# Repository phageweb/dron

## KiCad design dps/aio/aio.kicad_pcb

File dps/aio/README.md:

# AIO H743 pro Pavo20 Pro

Jedna deska místo MicoAir H743 AIO: STM32H743 s ArduPilotem, 4× ESC s AM32,
napájení VTX a LD06. Vychází z [OpenAIO](https://github.com/OpenDrone-hw/OpenAIO)
`986ce1e` (CERN-OHL-S-2.0), viz [návrh](../docs/02_navrh.md) a [požadavky](../docs/04_pozadavky.md).

Stav **21. 10. 2026: hlavní deska 22 nespojených, pracovní varianta MicoAir V2
po trasování 21 nespojených; obě 0 DRC chyb kategorie error.** Spoje nejsou hotové.
Nová kontrola, výsledek trasování a zbývající varování jsou v
[STAV-2026-10-21.md](./STAV-2026-10-21.md).
**Aktuální zadání: rešerše a předávka pro dokončení přes rozmístění součástek.**
Závěry, zdroje a návrh jsou v [RESERSE_LAYOUTU_V2.md](./RESERSE_LAYOUTU_V2.md),
konkrétní kroky a archiv správného výchozího projektu v
[PREDAVKA_LAYOUTU_V2.md](./PREDAVKA_LAYOUTU_V2.md). Tato předávka nahrazuje starší
doporučení pokračovat plošným přetrasováním.
Probíhá přechod k opakovatelnému postupu a referenci MicoAir743v2-AIO-45A;
připravená varianta má samostatné schéma, desku a hwdef, viz
[AUTOMATIZACE.md](./AUTOMATIZACE.md). Převzaté a jisté části jsou nakreslené,
včetně jádra H743 (napájení podle AN4938, piny podle hwdefu MicoAiru), krystalu,
barometru, druhé IMU ICM-42688-P, microSD, konektorů periferií, RGB LED a spínače bzučáku.

- **[NAVRH.md](./NAVRH.md)**: celý návrh, co je kde, proč a odkud, mapa pinů, kusovník.
- **Schéma se generuje**: `nix develop ./dps -c python3 dps/aio/gen/gen_aio.py` přepíše všechny
  listy (`*.kicad_sch`) se stálými UUID. Schéma se proto mění v `gen/gen_aio.py`, ne v KiCadu.
  Desku, pravidla, projekt a `lib.pretty` generátor nepřepisuje, ty se upravují v KiCadu.
- **[hwdef/](./hwdef/README.md)**: popis desky pro ArduPilot (firmware, bootloader, výchozí parametry).
- **Interaktivní schéma**: `nix develop ./dps -c python3 dps/aio/web/build.py` vytvoří
  `web/schema.html` (listy s klikacími bloky, texty v `web/obsah.py`).

```sh
nix develop ./dps
kicad dps/aio/aio.kicad_pro
```

## Listy

| List | Soubor | Stav | Odkud |
| --- | --- | --- | --- |
| kořen | `aio.kicad_sch` | nakreslený | vstup baterie, shunt 0,2 mΩ + INA186A3 (proud všech ESC), obrys s pady U24, testovací body z OpenAIO |
| ESC1–ESC4 | `esc_channel.kicad_sch` | **převzatý beze změny** | OpenAIO = kanál OpenESC: AT32F421 + NSG2065Q + 6× DOY180N03T, AM32 |
| Power | `fc_power.kicad_sch` | **převzatý beze změny** | +10V pro budiče ESC (stálé), +5V 3 A, USB OR na +4v5, 3,3 V TLV76733 1 A, 1,8 V pro gyro |
| IMU | `fc_imu.kicad_sch` | **převzatý beze změny** | BMI270 na SPI, napájení 1,8 V |
| VTX a LD06 | `vtx.kicad_sch` | nový | spínač TPS22810 z +10V pro HD VTX, HD VTX SH1.0-6P s pinoutem DJI, pady LD06 |
| MCU H743 | `mcu_h743.kicad_sch` | nakreslený | H743 s blokováním, krystal, BOOT0, SWD, USB-C, dělič baterie, I2C2 s barometrem, ICM-42688-P na SPI2, microSD, RGB LED, bzučák. Ostatní piny mají štítky podle hwdefu |

Vypuštěné z OpenAIO, protože patří k RP2354A nebo je nepotřebujeme: `fc_rp2350a`
(jádro), `rx_esp32c3_sx1281` (přijímač, máme XR1 Nano), `fc_osd` (analogové OSD),
`fc_pads` (pady, konektor SH-6, baro BMP580), `fc_blackbox` (microSD na SPI).

Proč spínač pro VTX: v OpenAIO napájí `+10V` zároveň budiče ESC i konektor
VTX. Kdyby se vypínala celá větev, vypnuly by se i motory. Proto VTX visí na `+10V`
až za spínačem TPS22810 s EN z MCU. Do 18. 10. tu byla kopie bucku U3, ale na desku
se nevešla.

## Deska

`aio.kicad_pcb` vychází z layoutu OpenAIO: 35,4 × 35,4 mm, 8 vrstev HDI 1+6+1, 1 oz.
Od 18. 10. odpovídá schématu: díly vypuštěných listů a jejich měď jsou pryč,
ESC, napájení, IMU a kořen zůstaly na místě i s vodiči. Nové díly mají **hrubé
rozmístění** (`aktualizuj_desku.sh --rozmisti --znovu`, pak `--vycisti`). Všechny čtyři
konektory periferií jako na MicoAir743-AIO jsou na hraně. Všech 82 nových dílů je na desce
(od 18. 10., kdy buck VTX nahradil spínač a BMI088 ICM-42688-P).
Po trasování zbývá 22 spojů ([NAVRH kap. 7](./NAVRH.md#7-deska-pcb)).

Schéma se do desky propisuje bez GUI (dělá totéž co F8, viz hlavička skriptu):

```sh
nix develop ./dps -c dps/aio/gen/aktualizuj_desku.sh       # --dry-run jen vypíše změny
kicad-cli pcb drc --schematic-parity --refill-zones dps/aio/aio.kicad_pcb
```

Před spuštěním zavři desku v KiCadu, jinak ji při uložení přepíše svou kopií.
Pro opakované kontroly a varianty použij `aktualizuj_desku.sh --auto`; pracuje na
kopii a uchová skutečné ERC/DRC reporty. Výsledky včetně známých výjimek jsou
popsané v [automatickém postupu](./AUTOMATIZACE.md).

## Kontrola

```sh
kicad-cli sch erc --severity-error dps/aio/aio.kicad_sch   # 18 chyb, všechny vysvětlené níž
```

| Počet | Co | Proč |
| ---: | --- | --- |
| 16 | `pin_not_driven` v ESC1–4 | převzaté z OpenAIO/OpenESC: piny kondenzátorů v jejich knihovně mají typ *input* |
| 1 | `pin_to_pin` VCAP E7–F8 | VCAP1 a VCAP2 spojené, jak doporučuje ST AN4938 |
| 1 | `pin_to_pin` QOD–VOUT U201 | QOD spojený s VOUT, aby se výstup po vypnutí vybil, podle datasheetu TPS22810 |

## Co je na tobě

Seznam s důvody je v [NAVRH.md, kap. 8](./NAVRH.md#8-otevřené-otázky): layout,
LCSC čísla nových dílů a ověření pinu 1 u konektorů GPS a MTF-02P. Schéma je od
17. 10. nakreslené celé. Obrys 35,4 mm a díry 25,5 zůstávají z OpenAIO (18. 10.),
oválné díry na 26 by zasáhly prokovy přívodu baterie.

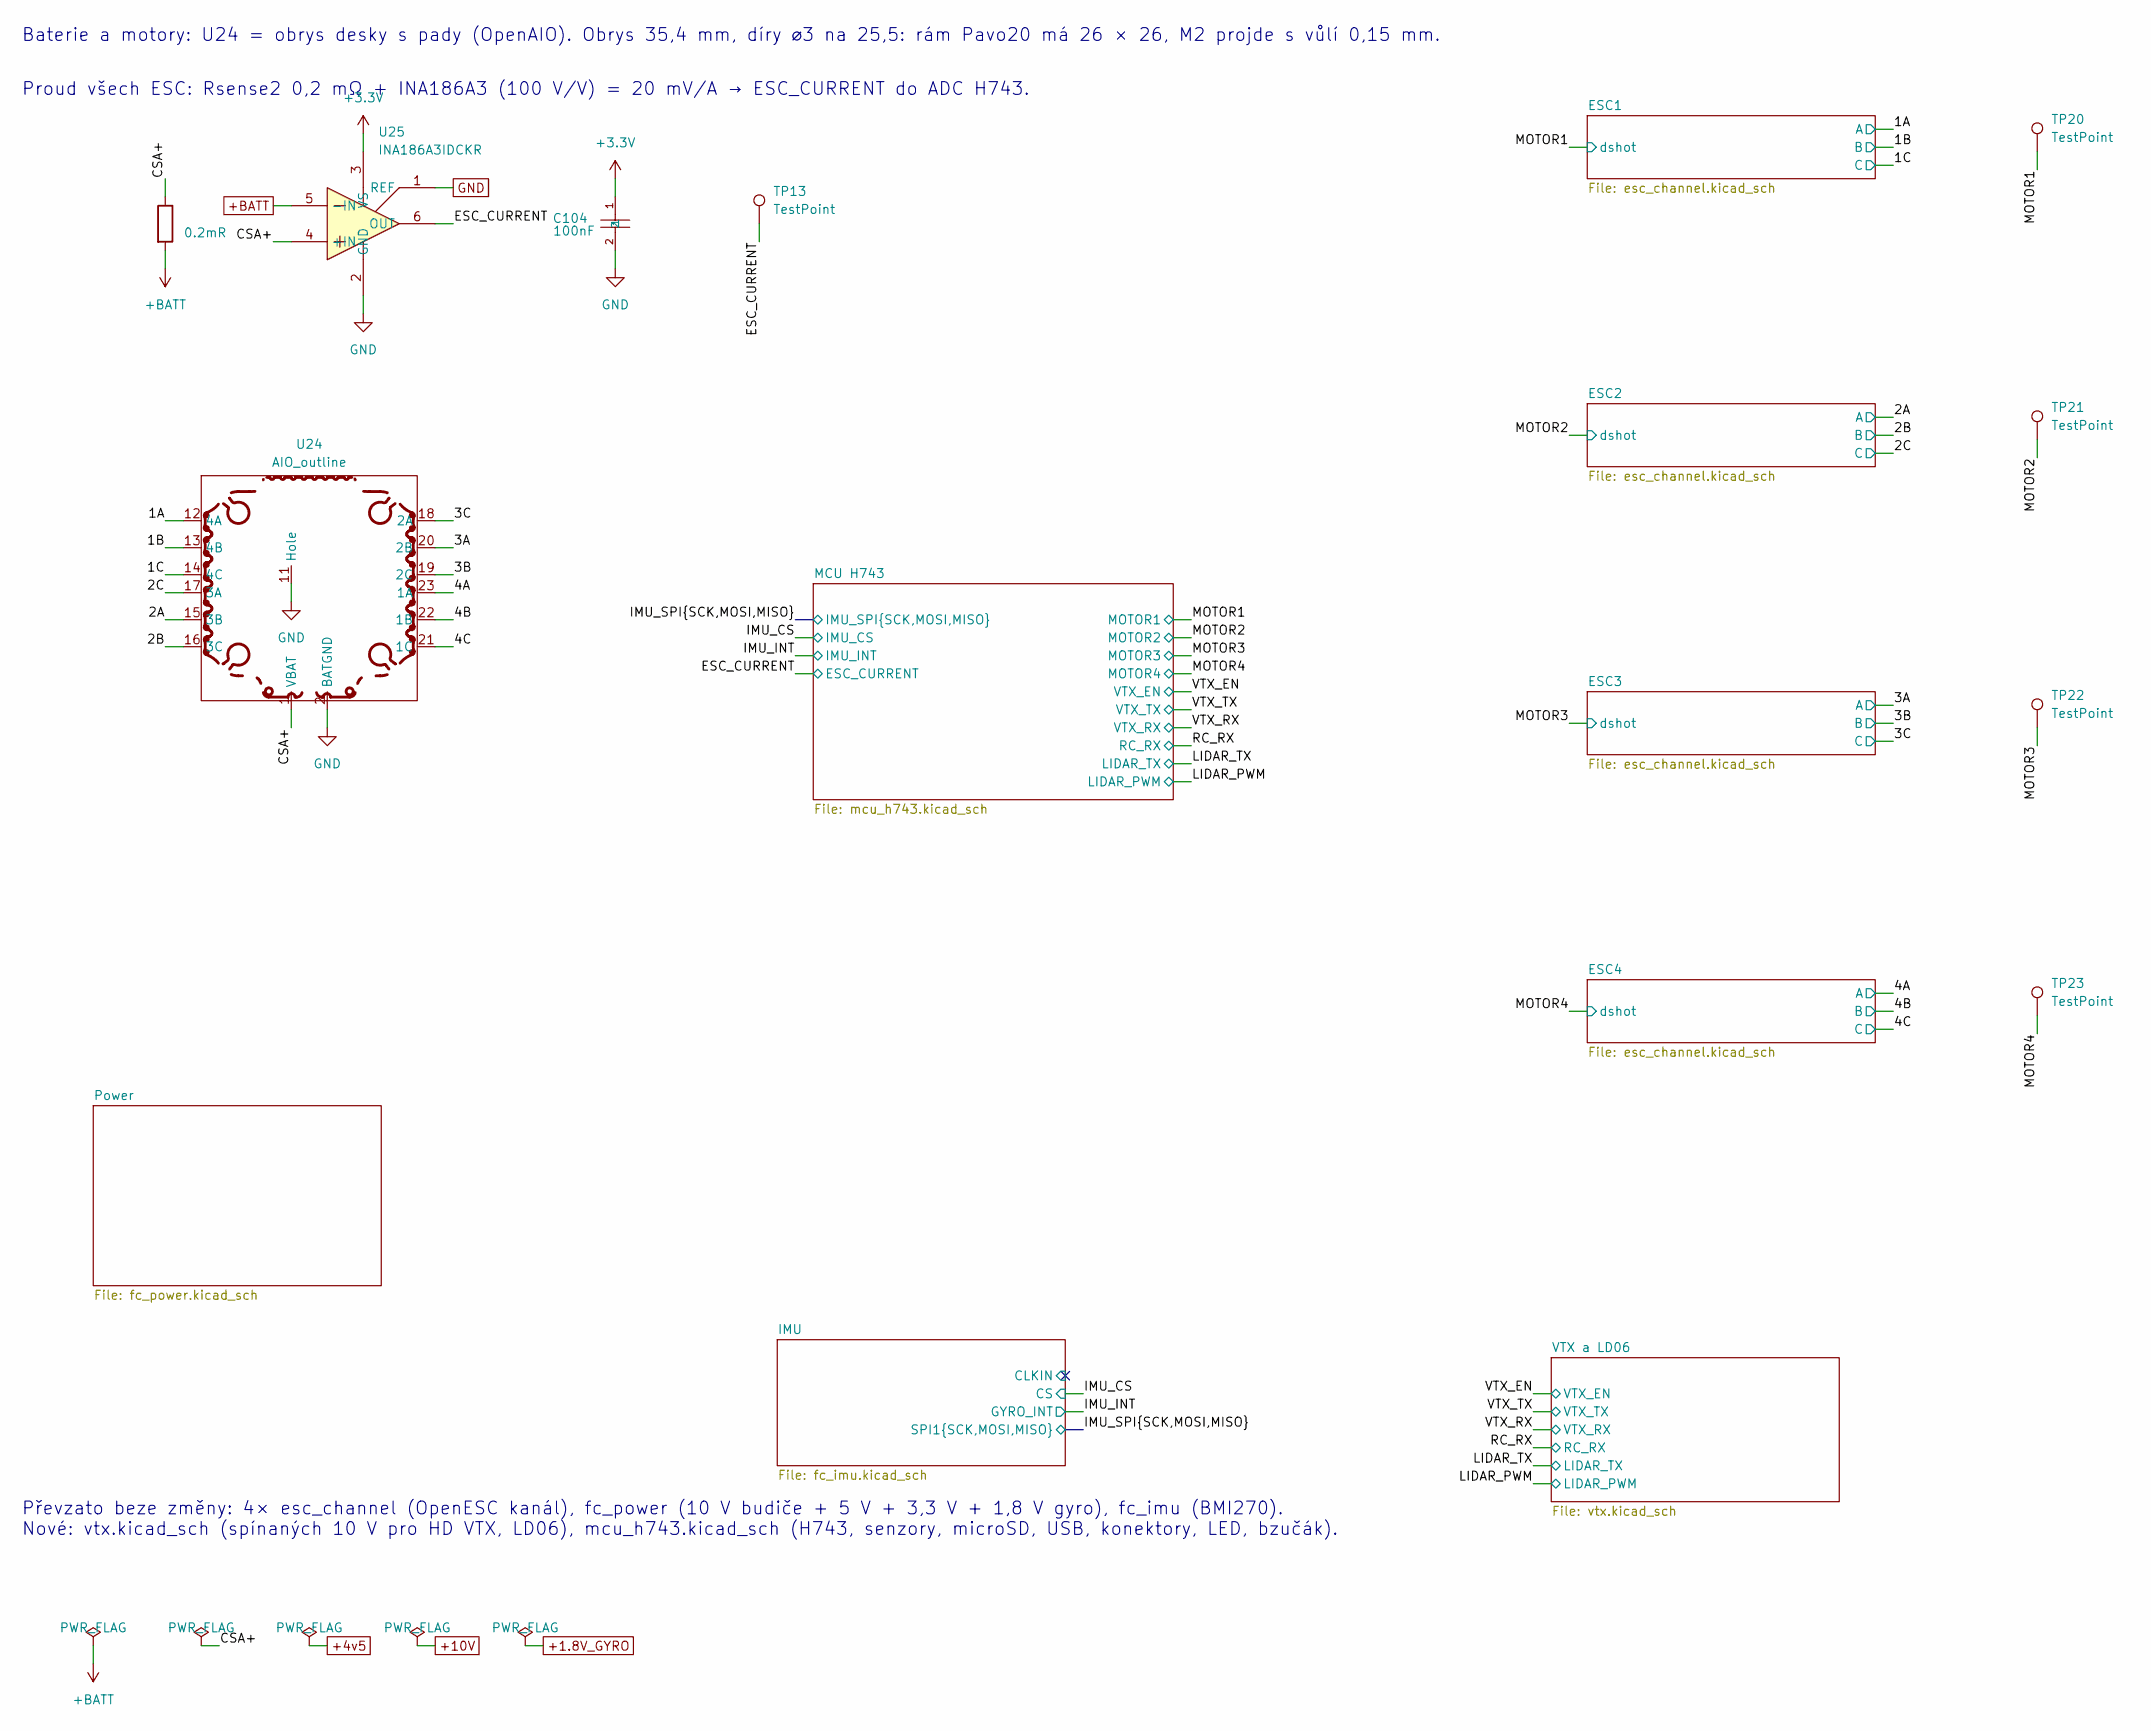
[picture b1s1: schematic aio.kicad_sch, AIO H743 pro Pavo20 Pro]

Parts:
C104: 100nF; C_0201_0603Metric; MPN GRM033R6YA104KE14D; LCSC C181043
Rsense2: 0.2mR; R_2512_6332Metric; MPN ASR-S-3-0.2F; LCSC C695806
TP13, TP20, TP21, TP22, TP23: TestPoint; TestPoint_Pad_D1.0mm
U24: AIO_outline
U25: INA186A3IDCKR; SOT-363_SC-70-6; MPN INA186A3IDCKR; LCSC C2058245

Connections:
+3.3V: C104.1, U25.3 (VS); also elsewhere on the board
+BATT: Rsense2.2, U25.5 (-IN); also elsewhere on the board
/1A: U24.12 (4A); also elsewhere on the board
/1B: U24.13 (4B); also elsewhere on the board
/1C: U24.14 (4C); also elsewhere on the board
/2A: U24.15 (3B); also elsewhere on the board
/2B: U24.16 (3C); also elsewhere on the board
/2C: U24.17 (3A); also elsewhere on the board
/3A: U24.20 (2B); also elsewhere on the board
/3B: U24.19 (2C); also elsewhere on the board
/3C: U24.18 (2A); also elsewhere on the board
/4A: U24.23 (1A); also elsewhere on the board
/4B: U24.22 (1B); also elsewhere on the board
/4C: U24.21 (1C); also elsewhere on the board
/CSA+: Rsense2.1, U24.1 (VBAT), U25.4 (+IN)
/ESC_CURRENT: TP13.1, U25.6 (OUT); also elsewhere on the board
GND: C104.2, U24.2 (BATGND), U24.11 (Hole), U25.1 (REF), U25.2 (GND); also elsewhere on the board

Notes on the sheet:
Baterie a motory: U24 = obrys desky s pady (OpenAIO). Obrys 35,4 mm, díry ⌀3 na 25,5: rám Pavo20 má 26 × 26, M2 projde s vůlí 0,15 mm.
Proud všech ESC: Rsense2 0,2 mΩ + INA186A3 (100 V/V) = 20 mV/A → ESC_CURRENT do ADC H743.
Převzato beze změny: 4× esc_channel (OpenESC kanál), fc_power (10 V budiče + 5 V + 3,3 V + 1,8 V gyro), fc_imu (BMI270). Nové: vtx.kicad_sch (spínaných 10 V pro HD VTX, LD06), mcu_h743.kicad_sch (H743, senzory, microSD, USB, konektory, LED, bzučák).

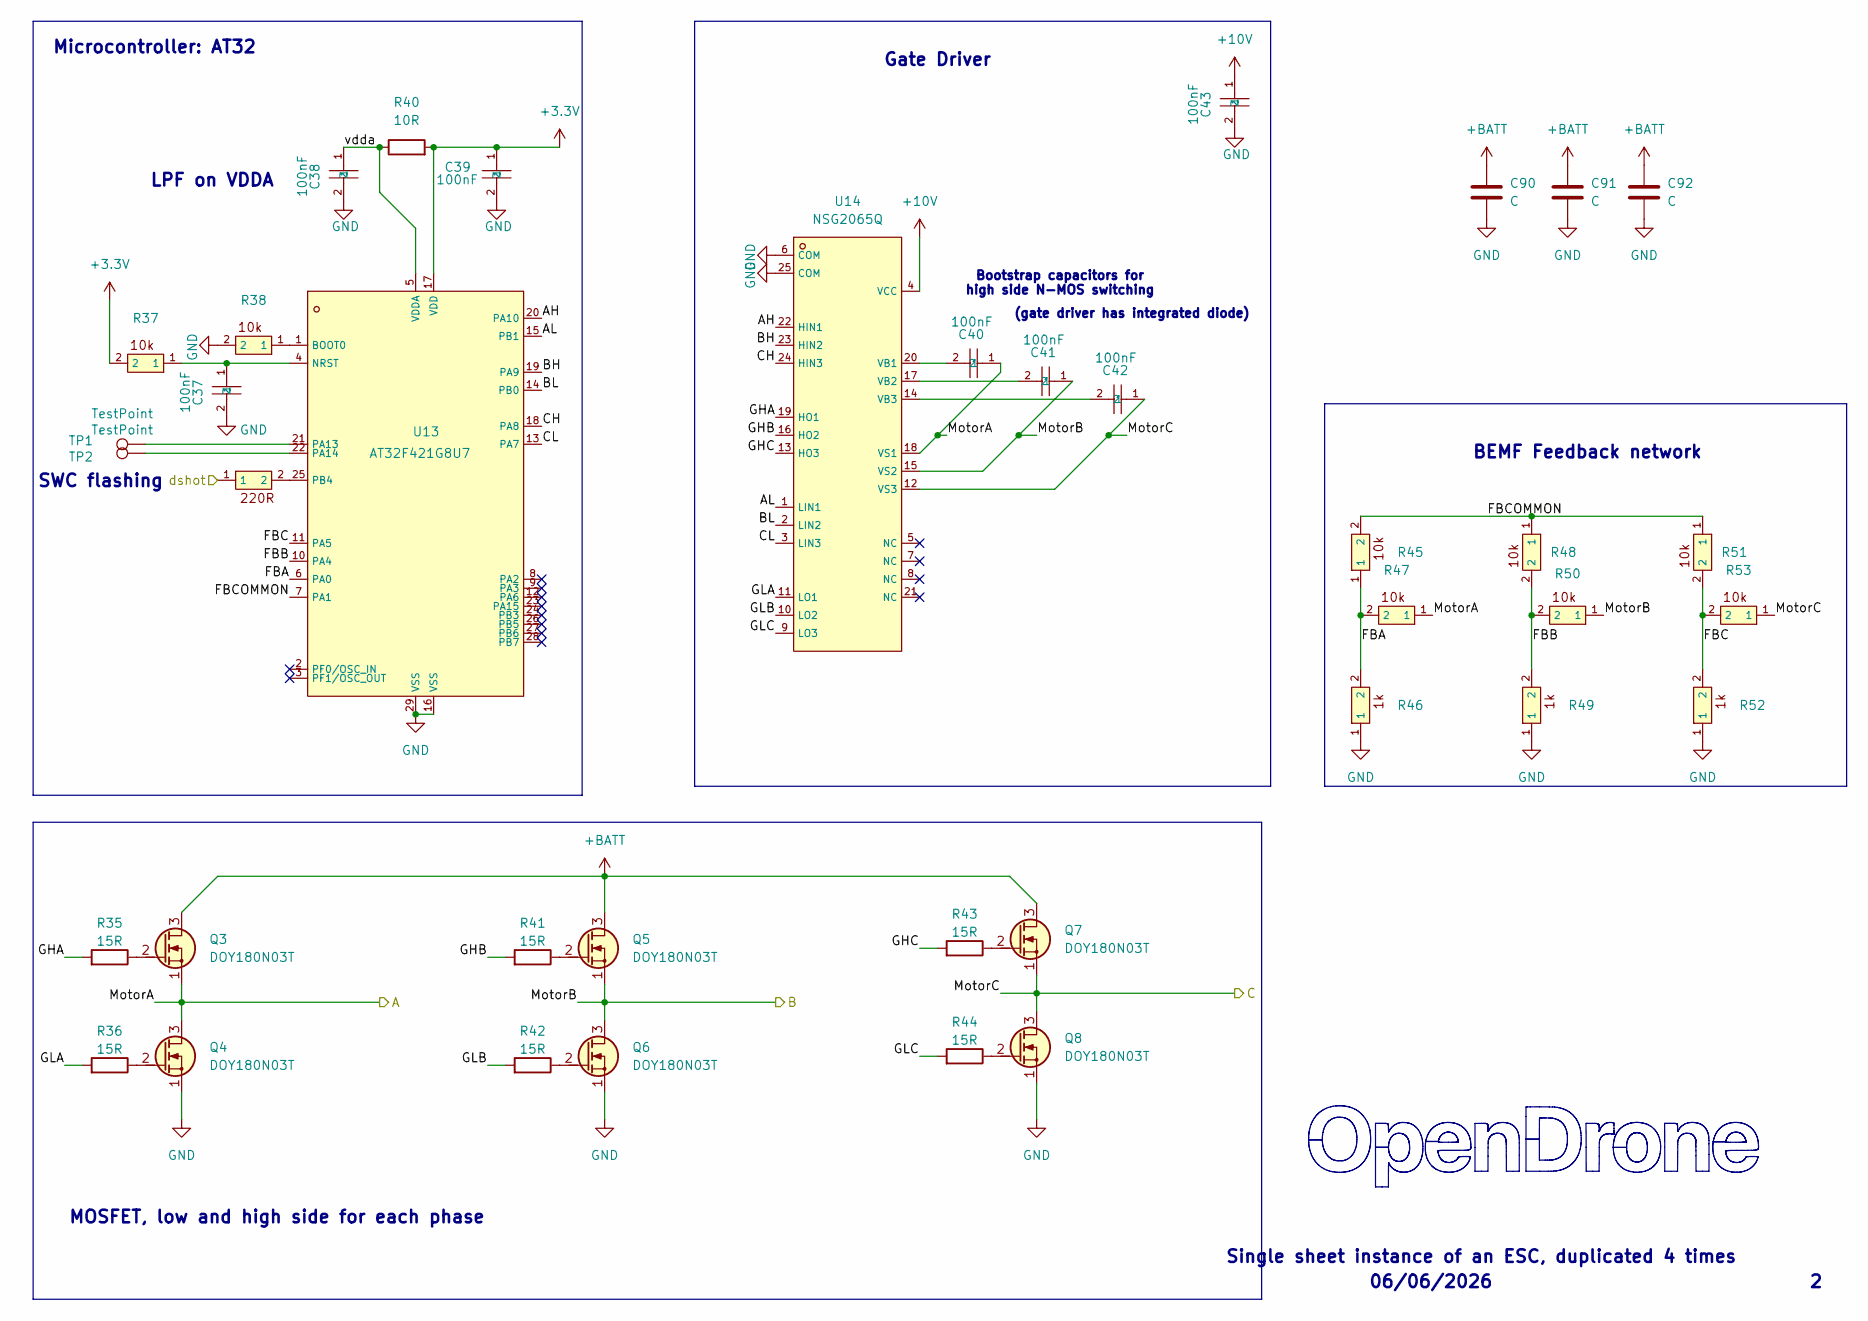
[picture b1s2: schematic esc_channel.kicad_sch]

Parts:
C37, C38, C39, C43: 100nF; C_0201_0603Metric; MPN GRM033R6YA104KE14D; LCSC C181043
C40, C41, C42: 100nF; C_0402_WIDE; MPN CL05B104KB54PNC; LCSC C307331
C90, C91, C92: C; C_0805_2012Metric
Q3, Q4, Q5, Q6, Q7, Q8: DOY180N03T; Diodes_PowerDI3333-8; MPN DOY180N03T; LCSC C49441966
R35, R36, R41, R42, R43, R44: 15R; R_0201_0603Metric; MPN 0201WMF150JTEE; LCSC C473542
R37, R38, R45, R47, R48, R50, R51, R53: 10k; R_0201_0603Metric; MPN RC0201FR-0710KL; LCSC C106225
R39: 220R; R_0201_0603Metric; MPN AC0201FR-07220RL; LCSC C226468
R40: 10R; R_0201_0603Metric; MPN RC0201FR-0710RL; LCSC C106226
R46, R49, R52: 1k; R_0201_0603Metric; MPN 0201WMF1001TEE; LCSC C270365
TP1, TP2: TestPoint; TestPoint_Pad_D1.0mm
U13: AT32F421G8U7; QFN-28_L4.0-W4.0-P0.40-TL-EP2.4; MPN AT32F421G8U7; LCSC C2765098
U14: NSG2065Q; QFN-24_L4.0-W4.0-P0.50-TL-EP2.8; MPN NSG2065Q; LCSC C41414478

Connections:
+3.3V: C39.1, R37.2, R40.2, U13.17 (VDD); also elsewhere on the board
+10V: C43.1, U14.4 (VCC); also elsewhere on the board
+BATT: C90.1, C91.1, C92.1, Q3.3 (D), Q5.3 (D), Q7.3 (D); also elsewhere on the board
/1A: C40.1, Q3.1 (S), Q4.3 (D), R47.1, U14.18 (VS1); also elsewhere on the board
/1B: C41.1, Q5.1 (S), Q6.3 (D), R50.1, U14.15 (VS2); also elsewhere on the board
/1C: C42.1, Q7.1 (S), Q8.3 (D), R53.1, U14.12 (VS3); also elsewhere on the board
/ESC1/AH: U13.20 (PA10), U14.22 (HIN1)
/ESC1/AL: U13.15 (PB1), U14.1 (LIN1)
/ESC1/BH: U13.19 (PA9), U14.23 (HIN2)
/ESC1/BL: U13.14 (PB0), U14.2 (LIN2)
/ESC1/CH: U13.18 (PA8), U14.24 (HIN3)
/ESC1/CL: U13.13 (PA7), U14.3 (LIN3)
/ESC1/FBA: R45.1, R46.2, R47.2, U13.6 (PA0)
/ESC1/FBB: R48.2, R49.2, R50.2, U13.10 (PA4)
/ESC1/FBC: R51.2, R52.2, R53.2, U13.11 (PA5)
/ESC1/FBCOMMON: R45.2, R48.1, R51.1, U13.7 (PA1)
/ESC1/GHA: R35.1, U14.19 (HO1)
/ESC1/GHB: R41.1, U14.16 (HO2)
/ESC1/GHC: R43.1, U14.13 (HO3)
/ESC1/GLA: R36.1, U14.11 (LO1)
/ESC1/GLB: R42.1, U14.10 (LO2)
/ESC1/GLC: R44.1, U14.9 (LO3)
/ESC1/vdda: C38.1, R40.1, U13.5 (VDDA)
/MOTOR1: R39.1; also elsewhere on the board
GND: C37.2, C38.2, C39.2, C43.2, C90.2, C91.2, C92.2, Q4.1 (S), Q6.1 (S), Q8.1 (S), R38.2, R46.1, R49.1, R52.1, U13.16 (VSS), U13.29 (VSS), U14.6 (COM), U14.25 (COM); also elsewhere on the board
unnamed: Q3.2 (G), R35.2
unnamed: Q4.2 (G), R36.2
unnamed: Q5.2 (G), R41.2
unnamed: Q6.2 (G), R42.2
unnamed: Q7.2 (G), R43.2
unnamed: Q8.2 (G), R44.2
unnamed: R38.1, U13.1 (BOOT0)
unnamed: C37.1, R37.1, U13.4 (NRST)
unnamed: TP1.1 (1_1), U13.21 (PA13)
unnamed: TP2.1 (1_1), U13.22 (PA14)
unnamed: R39.2, U13.25 (PB4)
unnamed: C40.2, U14.20 (VB1)
unnamed: C41.2, U14.17 (VB2)
unnamed: C42.2, U14.14 (VB3)

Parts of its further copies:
C44, C45, C46, C48, C50, C51, C52, C57, C58, C60, C64: 100nF; C_0201_0603Metric; MPN GRM033R6YA104KE14D; LCSC C181043
C47, C49, C53, C54, C55, C56, C59, C61, C62, C63: 100nF; C_0402_WIDE; MPN CL05B104KB54PNC; LCSC C307331
C93, C94, C95, C96, C97, C98, C99, C100, C101: C; C_0805_2012Metric
Q9, Q10, Q11, Q12, Q13, Q14, Q15, Q16, Q17, Q18, Q19, Q20, Q21, Q22, Q23, Q24, Q25, Q26: DOY180N03T; Diodes_PowerDI3333-8; MPN DOY180N03T; LCSC C49441966
R55, R60, R61, R62, R63, R73, R79, R80, R81, R82, R92, R93, R98, R99, R100, R101: 15R; R_0201_0603Metric; MPN 0201WMF150JTEE; LCSC C473542
R56, R57, R64, R66, R67, R69, R70, R72, R75, R83, R85, R86, R88, R89, R91, R94, R95, R102, R104, R105, R107, R108, R110: 10k; R_0201_0603Metric; MPN RC0201FR-0710KL; LCSC C106225
R58, R77, R96: 220R; R_0201_0603Metric; MPN AC0201FR-07220RL; LCSC C226468
R65, R68, R71, R84, R87, R90, R103, R106, R109: 1k; R_0201_0603Metric; MPN 0201WMF1001TEE; LCSC C270365
R78, R97: 10R; R_0201_0603Metric; MPN RC0201FR-0710RL; LCSC C106226
TP3, TP4, TP5, TP6, TP7, TP8: TestPoint; TestPoint_Pad_D1.0mm
U15, U17, U19: AT32F421G8U7; QFN-28_L4.0-W4.0-P0.40-TL-EP2.4; MPN AT32F421G8U7; LCSC C2765098
U16, U18, U20: NSG2065Q; QFN-24_L4.0-W4.0-P0.50-TL-EP2.8; MPN NSG2065Q; LCSC C41414478

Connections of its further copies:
+3.3V: C46.1, C53.1, C60.1, R56.2, R75.2, R78.2, R94.2, R97.2, U15.17 (VDD), U17.17 (VDD), U19.17 (VDD); also elsewhere on the board
+10V: C50.1, C57.1, C64.1, U16.4 (VCC), U18.4 (VCC), U20.4 (VCC); also elsewhere on the board
+BATT: C93.1, C94.1, C95.1, C96.1, C97.1, C98.1, C99.1, C100.1, C101.1, Q9.3 (D), Q11.3 (D), Q13.3 (D), Q15.3 (D), Q17.3 (D), Q19.3 (D), Q21.3 (D), Q23.3 (D), Q25.3 (D); also elsewhere on the board
/2A: C47.1, Q9.1 (S), Q10.3 (D), R66.1, U16.18 (VS1); also elsewhere on the board
/2B: C48.1, Q11.1 (S), Q12.3 (D), R69.1, U16.15 (VS2); also elsewhere on the board
/2C: C49.1, Q13.1 (S), Q14.3 (D), R72.1, U16.12 (VS3); also elsewhere on the board
/3A: C54.1, Q15.1 (S), Q16.3 (D), R85.1, U18.18 (VS1); also elsewhere on the board
/3B: C55.1, Q17.1 (S), Q18.3 (D), R88.1, U18.15 (VS2); also elsewhere on the board
/3C: C56.1, Q19.1 (S), Q20.3 (D), R91.1, U18.12 (VS3); also elsewhere on the board
/4A: C61.1, Q21.1 (S), Q22.3 (D), R104.1, U20.18 (VS1); also elsewhere on the board
/4B: C62.1, Q23.1 (S), Q24.3 (D), R107.1, U20.15 (VS2); also elsewhere on the board
/4C: C63.1, Q25.1 (S), Q26.3 (D), R110.1, U20.12 (VS3); also elsewhere on the board
/ESC2/AH: U15.20 (PA10), U16.22 (HIN1)
/ESC2/AL: U15.15 (PB1), U16.1 (LIN1)
/ESC2/BH: U15.19 (PA9), U16.23 (HIN2)
/ESC2/BL: U15.14 (PB0), U16.2 (LIN2)
/ESC2/CH: U15.18 (PA8), U16.24 (HIN3)
/ESC2/CL: U15.13 (PA7), U16.3 (LIN3)
/ESC2/FBA: R64.1, R65.2, R66.2, U15.6 (PA0)
/ESC2/FBB: R67.2, R68.2, R69.2, U15.10 (PA4)
/ESC2/FBC: R70.2, R71.2, R72.2, U15.11 (PA5)
/ESC2/FBCOMMON: R64.2, R67.1, R70.1, U15.7 (PA1)
/ESC2/GHA: U16.19 (HO1); also elsewhere on the board
/ESC2/GHB: R60.1, U16.16 (HO2)
/ESC2/GHC: R62.1, U16.13 (HO3)
/ESC2/GLA: R55.1, U16.11 (LO1)
/ESC2/GLB: R61.1, U16.10 (LO2)
/ESC2/GLC: R63.1, U16.9 (LO3)
/ESC2/vdda: C45.1, U15.5 (VDDA); also elsewhere on the board
/ESC3/AH: U17.20 (PA10), U18.22 (HIN1)
/ESC3/AL: U17.15 (PB1), U18.1 (LIN1)
/ESC3/BH: U17.19 (PA9), U18.23 (HIN2)
/ESC3/BL: U17.14 (PB0), U18.2 (LIN2)
/ESC3/CH: U17.18 (PA8), U18.24 (HIN3)
/ESC3/CL: U17.13 (PA7), U18.3 (LIN3)
/ESC3/FBA: R83.1, R84.2, R85.2, U17.6 (PA0)
/ESC3/FBB: R86.2, R87.2, R88.2, U17.10 (PA4)
/ESC3/FBC: R89.2, R90.2, R91.2, U17.11 (PA5)
/ESC3/FBCOMMON: R83.2, R86.1, R89.1, U17.7 (PA1)
/ESC3/GHA: R73.1, U18.19 (HO1)
/ESC3/GHB: R79.1, U18.16 (HO2)
/ESC3/GHC: R81.1, U18.13 (HO3)
/ESC3/GLA: U18.11 (LO1); also elsewhere on the board
/ESC3/GLB: R80.1, U18.10 (LO2)
/ESC3/GLC: R82.1, U18.9 (LO3)
/ESC3/vdda: C52.1, R78.1, U17.5 (VDDA)
/ESC4/AH: U19.20 (PA10), U20.22 (HIN1)
/ESC4/AL: U19.15 (PB1), U20.1 (LIN1)
/ESC4/BH: U19.19 (PA9), U20.23 (HIN2)
/ESC4/BL: U19.14 (PB0), U20.2 (LIN2)
/ESC4/CH: U19.18 (PA8), U20.24 (HIN3)
/ESC4/CL: U19.13 (PA7), U20.3 (LIN3)
/ESC4/FBA: R102.1, R103.2, R104.2, U19.6 (PA0)
/ESC4/FBB: R105.2, R106.2, R107.2, U19.10 (PA4)
/ESC4/FBC: R108.2, R109.2, R110.2, U19.11 (PA5)
/ESC4/FBCOMMON: R102.2, R105.1, R108.1, U19.7 (PA1)
/ESC4/GHA: R92.1, U20.19 (HO1)
/ESC4/GHB: R98.1, U20.16 (HO2)
/ESC4/GHC: R100.1, U20.13 (HO3)
/ESC4/GLA: R93.1, U20.11 (LO1)
/ESC4/GLB: R99.1, U20.10 (LO2)
/ESC4/GLC: R101.1, U20.9 (LO3)
/ESC4/vdda: C59.1, R97.1, U19.5 (VDDA)
/MOTOR2: R58.1; also elsewhere on the board
/MOTOR3: R77.1; also elsewhere on the board
/MOTOR4: R96.1; also elsewhere on the board
GND: C44.2, C45.2, C46.2, C50.2, C51.2, C52.2, C53.2, C57.2, C58.2, C59.2, C60.2, C64.2, C93.2, C94.2, C95.2, C96.2, C97.2, C98.2, C99.2, C100.2, C101.2, Q10.1 (S), Q12.1 (S), Q14.1 (S), Q16.1 (S), Q18.1 (S), Q20.1 (S), Q22.1 (S), Q24.1 (S), Q26.1 (S), R57.2, R65.1, R68.1, R71.1, R84.1, R87.1, R90.1, R95.2, R103.1, R106.1, R109.1, U15.16 (VSS), U15.29 (VSS), U16.6 (COM), U16.25 (COM), U17.16 (VSS), U17.29 (VSS), U18.6 (COM), U18.25 (COM), U19.16 (VSS), U19.29 (VSS), U20.6 (COM), U20.25 (COM); also elsewhere on the board
unnamed 171: Q9.2 (G); also elsewhere on the board
unnamed: Q10.2 (G), R55.2
unnamed: Q11.2 (G), R60.2
unnamed: Q12.2 (G), R61.2
unnamed: Q13.2 (G), R62.2
unnamed: Q14.2 (G), R63.2
unnamed: Q15.2 (G), R73.2
unnamed 178: Q16.2 (G); also elsewhere on the board
unnamed: Q17.2 (G), R79.2
unnamed: Q18.2 (G), R80.2
unnamed: Q19.2 (G), R81.2
unnamed: Q20.2 (G), R82.2
unnamed: Q21.2 (G), R92.2
unnamed: Q22.2 (G), R93.2
unnamed: Q23.2 (G), R98.2
unnamed: Q24.2 (G), R99.2
unnamed: Q25.2 (G), R100.2
unnamed: Q26.2 (G), R101.2
unnamed: R57.1, U15.1 (BOOT0)
unnamed: C44.1, R56.1, U15.4 (NRST)
unnamed: TP3.1 (1_1), U15.21 (PA13)
unnamed: TP4.1 (1_1), U15.22 (PA14)
unnamed: R58.2, U15.25 (PB4)
unnamed: C47.2, U16.20 (VB1)
unnamed: C48.2, U16.17 (VB2)
unnamed: C49.2, U16.14 (VB3)
unnamed 211: U17.1 (BOOT0); also elsewhere on the board
unnamed: C51.1, R75.1, U17.4 (NRST)
unnamed: TP5.1 (1_1), U17.21 (PA13)
unnamed: TP6.1 (1_1), U17.22 (PA14)
unnamed: R77.2, U17.25 (PB4)
unnamed: C54.2, U18.20 (VB1)
unnamed: C55.2, U18.17 (VB2)
unnamed: C56.2, U18.14 (VB3)
unnamed: R95.1, U19.1 (BOOT0)
unnamed: C58.1, R94.1, U19.4 (NRST)
unnamed: TP7.1 (1_1), U19.21 (PA13)
unnamed: TP8.1 (1_1), U19.22 (PA14)
unnamed: R96.2, U19.25 (PB4)
unnamed: C61.2, U20.20 (VB1)
unnamed: C62.2, U20.17 (VB2)
unnamed: C63.2, U20.14 (VB3)

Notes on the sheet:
Bootstrap capacitors for high side N-MOS switching
Gate Driver
MOSFET, low and high side for each phase
Single sheet instance of an ESC, duplicated 4 times
Microcontroller: AT32
SWC flashing
(gate driver has integrated diode)
06/06/2026
BEMF Feedback network
LPF on VDDA

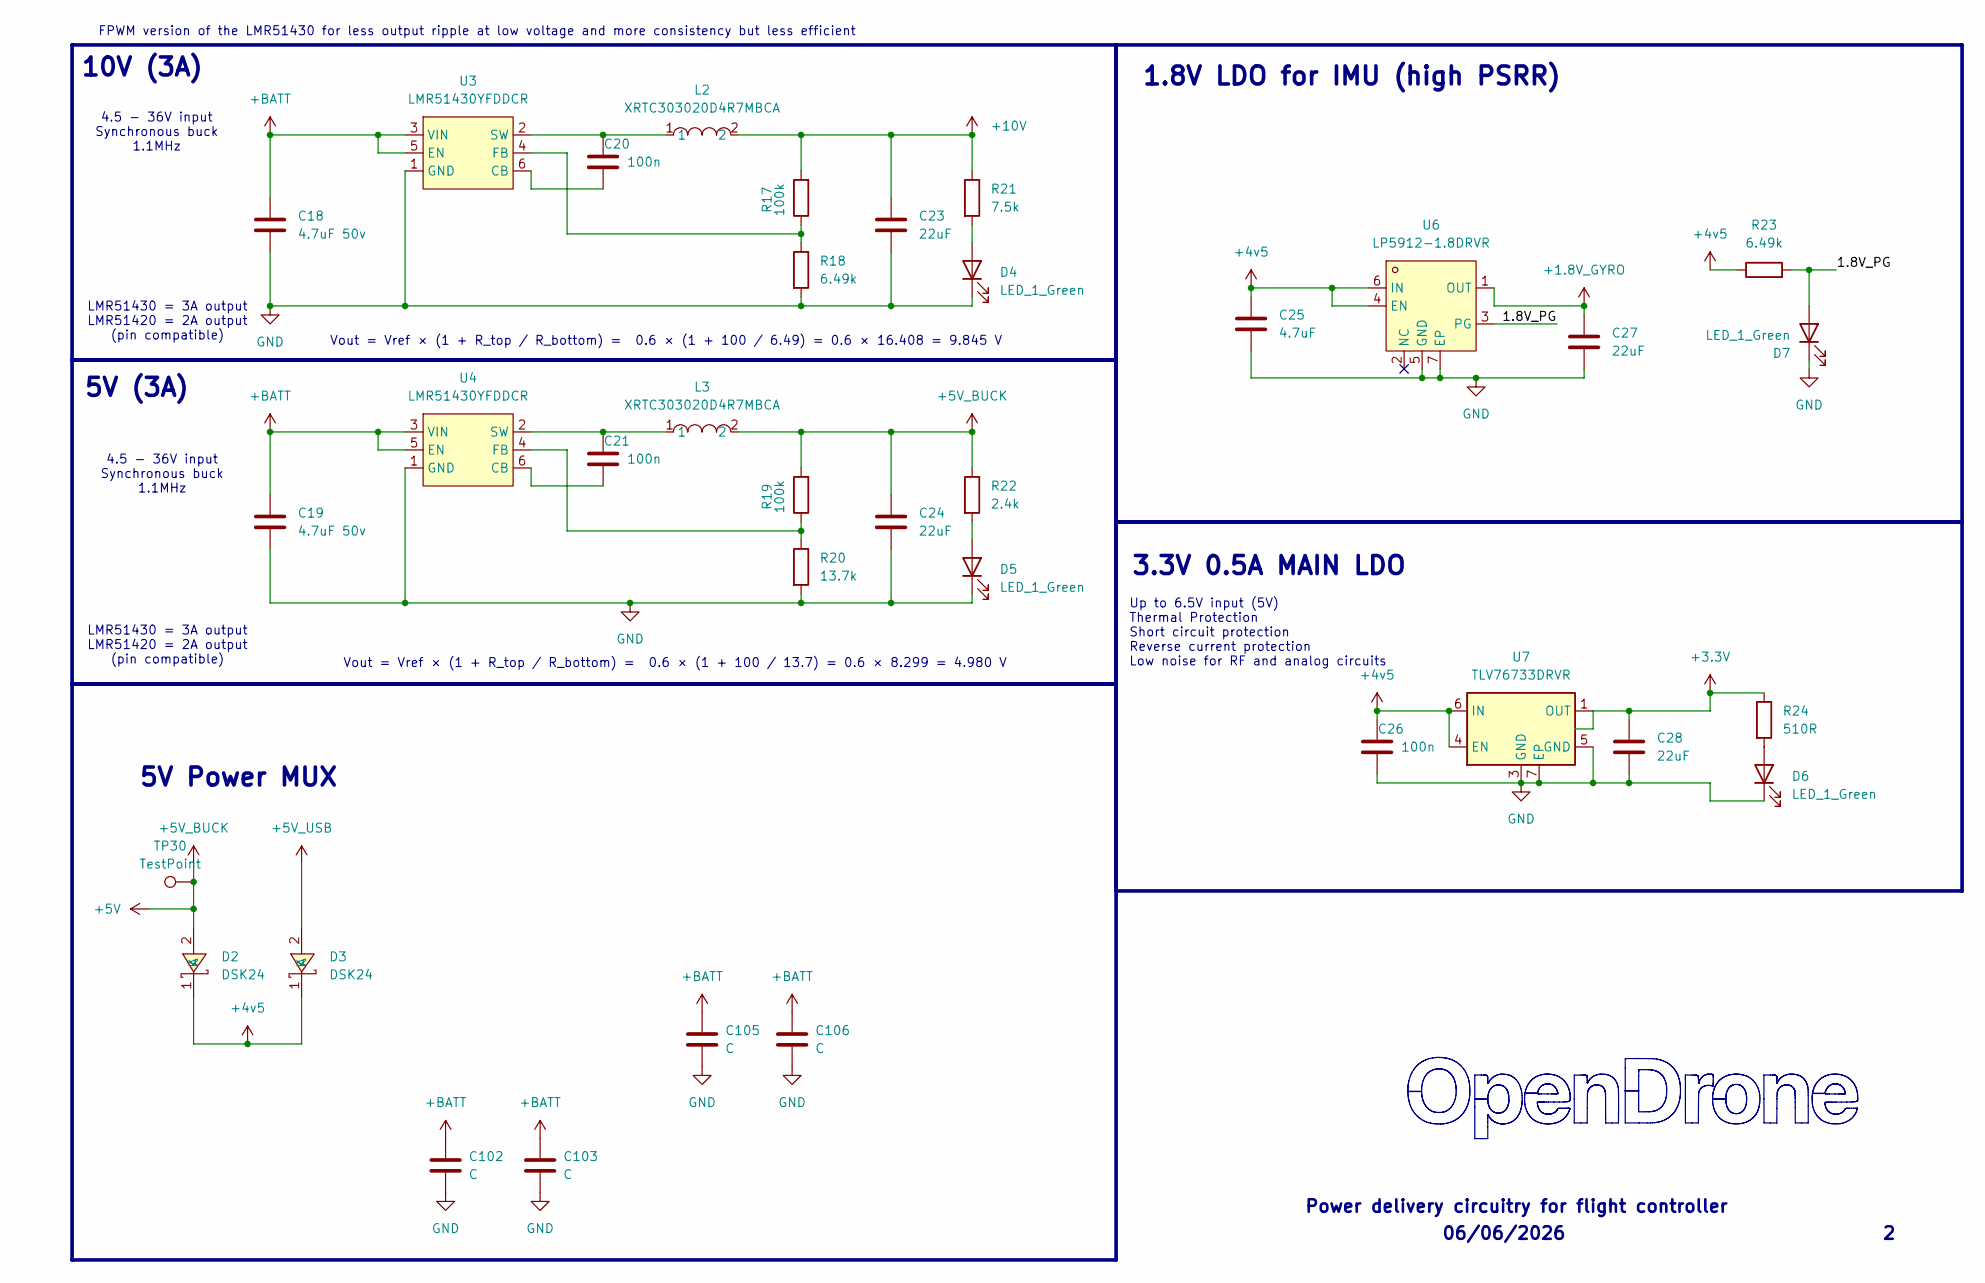
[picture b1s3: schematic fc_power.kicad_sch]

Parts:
C18, C19: 4.7uF 50v; C_0805_2012Metric; MPN CL21A475KBQNNNE; LCSC C98192
C20, C21, C26: 100n; C_0201_0603Metric; MPN GRM033R61E104KE14D; LCSC C76939
C23, C24: 22uF; C_0603_1608Metric; MPN CL10A226MO7JZNC; LCSC C2762594
C25: 4.7uF; C_0402_1005Metric; MPN CL05A475MP5NRNC; LCSC C23733
C27, C28: 22uF; C_0402_1005Metric; MPN GRM155R60J226ME11D; LCSC C415703
C102, C103: C; C_0805_2012Metric
C105, C106: C; C_1206_3216Metric
D2, D3: DSK24; SOD-123_L2.8-W1.8-LS3.7-RD; MPN DSK24; LCSC C64890
D4, D5, D6, D7: LED_1_Green; LED_0402_1005Metric; MPN XL-1005UGC; LCSC C965793
L2, L3: XRTC303020D4R7MBCA; IND-SMD_L3.0-W3.0_AFE303020S; MPN XRTC303020D4R7MBCA; LCSC C39846837
R17, R19: 100k; R_0201_0603Metric; MPN 0201WMF1003TEE; LCSC C270364
R18, R23: 6.49k; R_0201_0603Metric; LCSC C2107920
R20: 13.7k; R_0201_0603Metric; MPN RC-01W1372FT; LCSC C320695
R21: 7.5k; R_0201_0603Metric; LCSC C474437
R22: 2.4k; R_0201_0603Metric; LCSC C166281
R24: 510R; R_0201_0603Metric; LCSC C57784
TP30: TestPoint; TestPoint_Pad_D1.0mm
U3, U4: LMR51430YFDDCR; SOT-23-6_L2.9-W1.6-P0.95-LS2.9-BL; MPN LMR51430YFDDCR; LCSC C5219261
U6: LP5912-1.8DRVR; WSON-6-1EP_2x2mm_P0.65mm_EP1x1.6mm_ThermalVias; MPN LP5912-1.8DRVR; LCSC C2876234
U7: TLV76733DRVR; WSON-6-1EP_2x2mm_P0.65mm_EP1x1.6mm; MPN TLV76733DRVR; LCSC C2848334

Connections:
+1.8V_GYRO: C27.1, U6.1 (OUT); also elsewhere on the board
+3.3V: C28.1, R24.1, U7.1 (OUT), U7.2 (SNS); also elsewhere on the board
+4v5: C25.1, C26.1, D2.1 (K), D3.1 (K), R23.1, U6.4 (EN), U6.6 (IN), U7.4 (EN), U7.6 (IN)
+5V: C24.1, D2.2 (A), L3.2, R19.2, R22.1, TP30.1; also elsewhere on the board
+5V_USB: D3.2 (A); also elsewhere on the board
+10V: C23.1, L2.2, R17.2, R21.1; also elsewhere on the board
+BATT: C18.1, C19.1, C102.1, C103.1, C105.1, C106.1, U3.3 (VIN), U3.5 (EN), U4.3 (VIN), U4.5 (EN); also elsewhere on the board
/Power/1.8V_PG: D7.2 (A), R23.2, U6.3 (PG)
GND: C18.2, C19.2, C23.2, C24.2, C25.2, C26.2, C27.2, C28.2, C102.2, C103.2, C105.2, C106.2, D4.1 (K), D5.1 (K), D6.1 (K), D7.1 (K), R18.2, R20.2, U3.1 (GND), U4.1 (GND), U6.5 (GND), U6.7 (EP), U7.3 (GND), U7.5 (GND), U7.7 (EP); also elsewhere on the board
unnamed: D4.2 (A), R21.2
unnamed: D5.2 (A), R22.2
unnamed: D6.2 (A), R24.2
unnamed: C20.2, U3.6 (CB)
unnamed: R17.1, R18.1, U3.4 (FB)
unnamed: C20.1, L2.1, U3.2 (SW)
unnamed: C21.2, U4.6 (CB)
unnamed: R19.1, R20.1, U4.4 (FB)
unnamed: C21.1, L3.1, U4.2 (SW)

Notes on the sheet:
Vout = Vref × (1 + R_top / R_bottom) = 0.6 × (1 + 100 / 13.7) = 0.6 × 8.299 = 4.980 V
1.8V LDO for IMU (high PSRR)
4.5 - 36V input Synchronous buck 1.1MHz
5V Power MUX
10V (3A)
3.3V 0.5A MAIN LDO
Up to 6.5V input (5V) Thermal Protection Short circuit protection Reverse current protection Low noise for RF and analog circuits
Vout = Vref × (1 + R_top / R_bottom) = 0.6 × (1 + 100 / 6.49) = 0.6 × 16.408 = 9.845 V
06/06/2026
FPWM version of the LMR51430 for less output ripple at low voltage and more consistency but less efficient
5V (3A)
LMR51430 = 3A output LMR51420 = 2A output (pin compatible)
Power delivery circuitry for flight controller

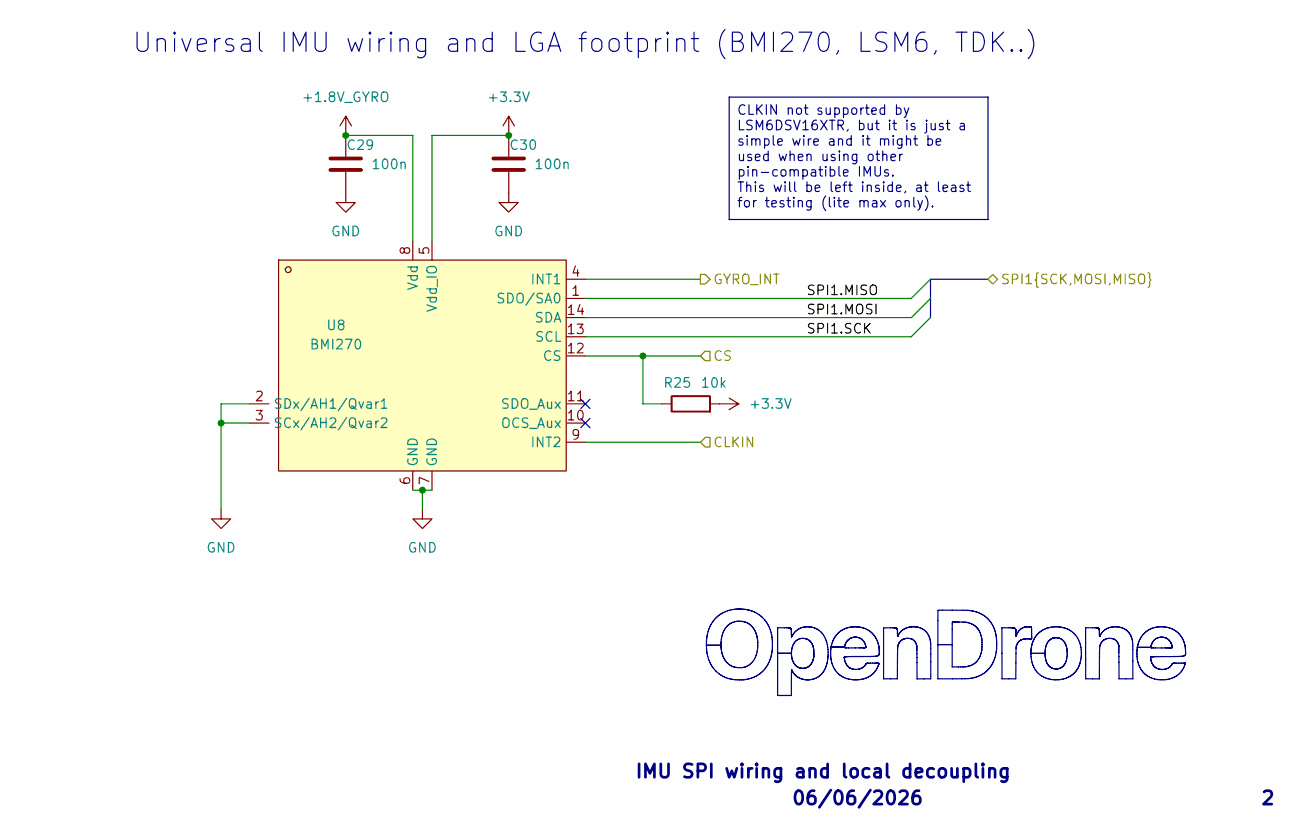
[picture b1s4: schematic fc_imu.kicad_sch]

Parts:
C29, C30: 100n; C_0201_0603Metric; MPN GRM033R61E104KE14D; LCSC C76939
R25: 10k; R_0201_0603Metric; MPN RC0201FR-0710KL; LCSC C106225
U8: BMI270; LGA-14_L3.0-W2.5-P0.50-BR; MPN BMI270; LCSC C2836813

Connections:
+1.8V_GYRO: C29.1, U8.8 (Vdd); also elsewhere on the board
+3.3V: C30.1, R25.2, U8.5 (Vdd_IO); also elsewhere on the board
/IMU/CLKIN: U8.9 (INT2)
/IMU_CS: R25.1, U8.12 (CS); also elsewhere on the board
/IMU_INT: U8.4 (INT1); also elsewhere on the board
/IMU_SPI.MISO: U8.1 (SDO/SA0); also elsewhere on the board
/IMU_SPI.MOSI: U8.14 (SDA); also elsewhere on the board
/IMU_SPI.SCK: U8.13 (SCL); also elsewhere on the board
GND: C29.2, C30.2, U8.2 (SDx/AH1/Qvar1), U8.3 (SCx/AH2/Qvar2), U8.6 (GND), U8.7 (GND); also elsewhere on the board

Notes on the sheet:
06/06/2026
Universal IMU wiring and LGA footprint (BMI270, LSM6, TDK..)
IMU SPI wiring and local decoupling
CLKIN not supported by LSM6DSV16XTR, but it is just a simple wire and it might be used when using other pin-compatible IMUs. This will be left inside, at least for testing (lite max only).

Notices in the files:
dps/aio/aio.kicad_sch:
Převzato z OpenAIO (CERN-OHL-S-2.0), https://github.com/OpenDrone-hw/OpenAIO
Licence: CERN-OHL-S-2.0
dps/aio/gen/gen_aio.py:
root.write("aio.kicad_sch", "AIO H743 pro Pavo20 Pro", ROOT, comments=[CERN, "Licence: CERN-OHL-S-2.0"])
v.write("vtx.kicad_sch", "VTX a LD06", uid(), comments=["Napájení VTX z +10V jako OpenAIO (CERN-OHL-S-2.0)", "Licence: CERN-OHL-S-2.0"])
